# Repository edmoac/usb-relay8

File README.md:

# USB relay 8

KiCad project of USB relay board, using STM32 microcontroller.

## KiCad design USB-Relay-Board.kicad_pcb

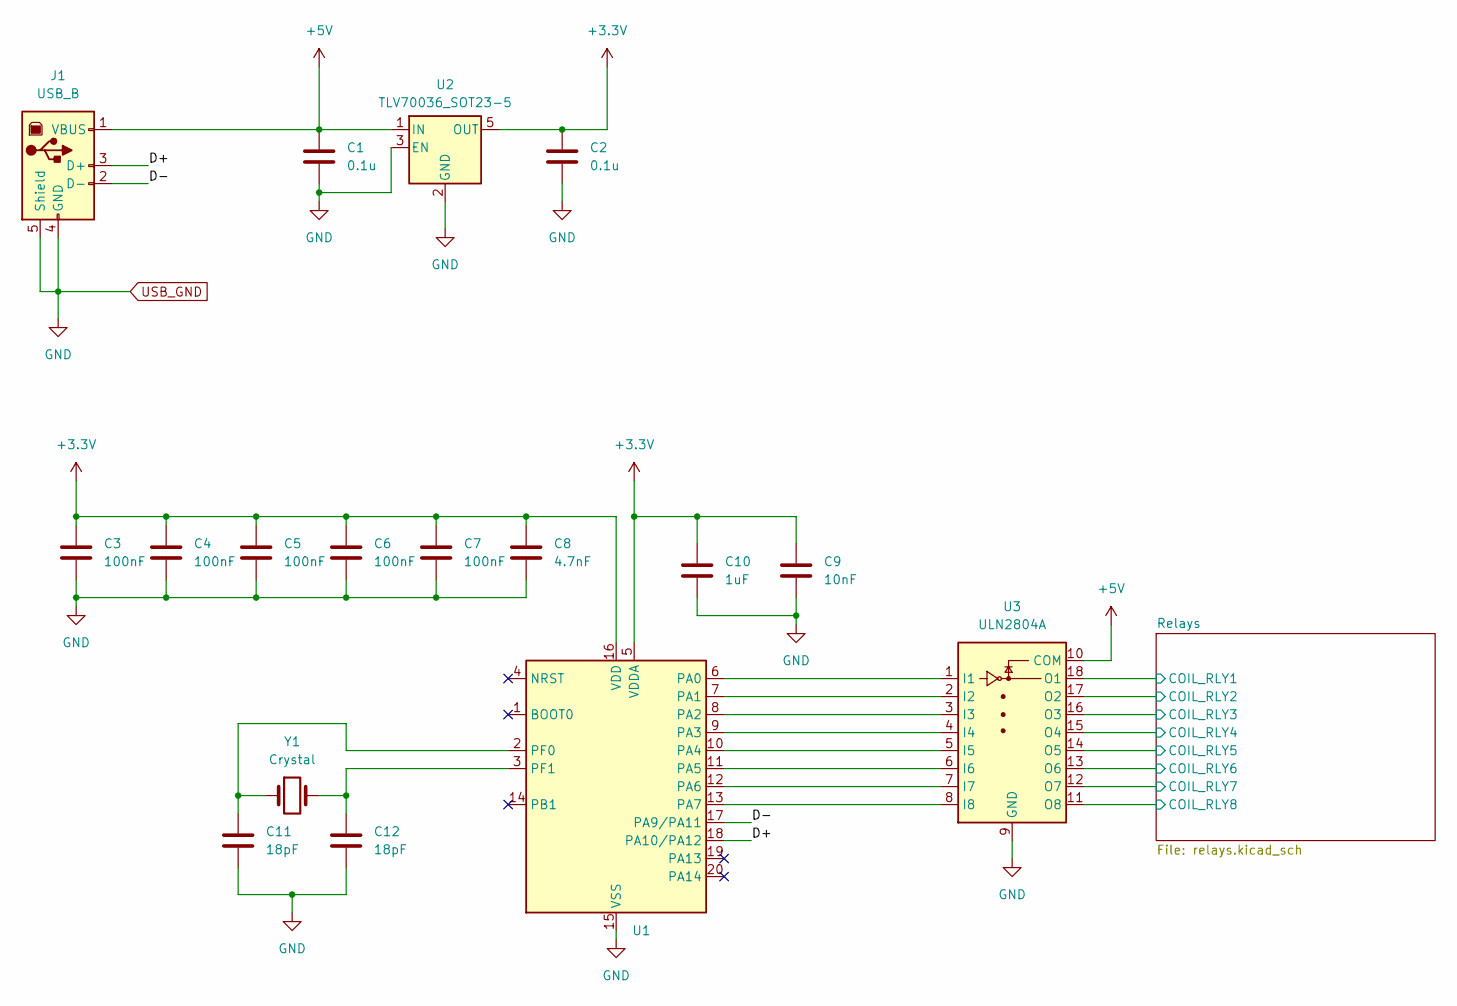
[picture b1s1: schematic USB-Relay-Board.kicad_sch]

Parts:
C1, C2: 0.1u; C_1206_3216Metric_Pad1.33x1.80mm_HandSolder
C3, C4, C5, C6, C7: 100nF; C_0805_2012Metric_Pad1.18x1.45mm_HandSolder
C8: 4.7nF; C_0805_2012Metric_Pad1.18x1.45mm_HandSolder
C9: 10nF; C_0805_2012Metric_Pad1.18x1.45mm_HandSolder
C10: 1uF; C_0805_2012Metric_Pad1.18x1.45mm_HandSolder
C11, C12: 18pF; C_0805_2012Metric_Pad1.18x1.45mm_HandSolder
J1: USB_B; USB_B_Lumberg_2411_02_Horizontal
U1: STM32F070F6Px; TSSOP-20_4.4x6.5mm_P0.65mm
U2: TLV70036_SOT23-5; SOT-23-5
U3: ULN2804A; DIP-18_W7.62mm_LongPads
Y1: Crystal; Crystal_HC18-U_Vertical

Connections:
+3.3V: C2.1, C3.1, C4.1, C5.1, C6.1, C7.1, C8.1, C9.1, C10.1, U1.5 (VDDA), U1.16 (VDD), U2.5 (OUT)
+5V: C1.1, J1.1 (VBUS), U2.1 (IN), U3.10 (COM)
/D+: J1.3 (D+), U1.18 (PA10/PA12)
/D-: J1.2 (D-), U1.17 (PA9/PA11)
/Relays/COIL_RLY1: U3.18 (O1); also elsewhere on the board
/Relays/COIL_RLY2: U3.17 (O2); also elsewhere on the board
/Relays/COIL_RLY3: U3.16 (O3); also elsewhere on the board
/Relays/COIL_RLY4: U3.15 (O4); also elsewhere on the board
/Relays/COIL_RLY5: U3.14 (O5); also elsewhere on the board
/Relays/COIL_RLY6: U3.13 (O6); also elsewhere on the board
/Relays/COIL_RLY7: U3.12 (O7); also elsewhere on the board
/Relays/COIL_RLY8: U3.11 (O8); also elsewhere on the board
unnamed: U1.6 (PA0), U3.1 (I1)
unnamed: U1.7 (PA1), U3.2 (I2)
unnamed: U1.8 (PA2), U3.3 (I3)
unnamed: U1.9 (PA3), U3.4 (I4)
unnamed: U1.10 (PA4), U3.5 (I5)
unnamed: U1.11 (PA5), U3.6 (I6)
unnamed: U1.12 (PA6), U3.7 (I7)
unnamed: U1.13 (PA7), U3.8 (I8)
unnamed: C11.1, U1.2 (PF0), Y1.1
unnamed: C12.1, U1.3 (PF1), Y1.2
USB_GND: C1.2, C2.2, C3.2, C4.2, C5.2, C6.2, C7.2, C8.2, C9.2, C10.2, C11.2, C12.2, J1.4 (GND), J1.5 (Shield), U1.15 (VSS), U2.2 (GND), U2.3 (EN), U3.9 (GND); also elsewhere on the board

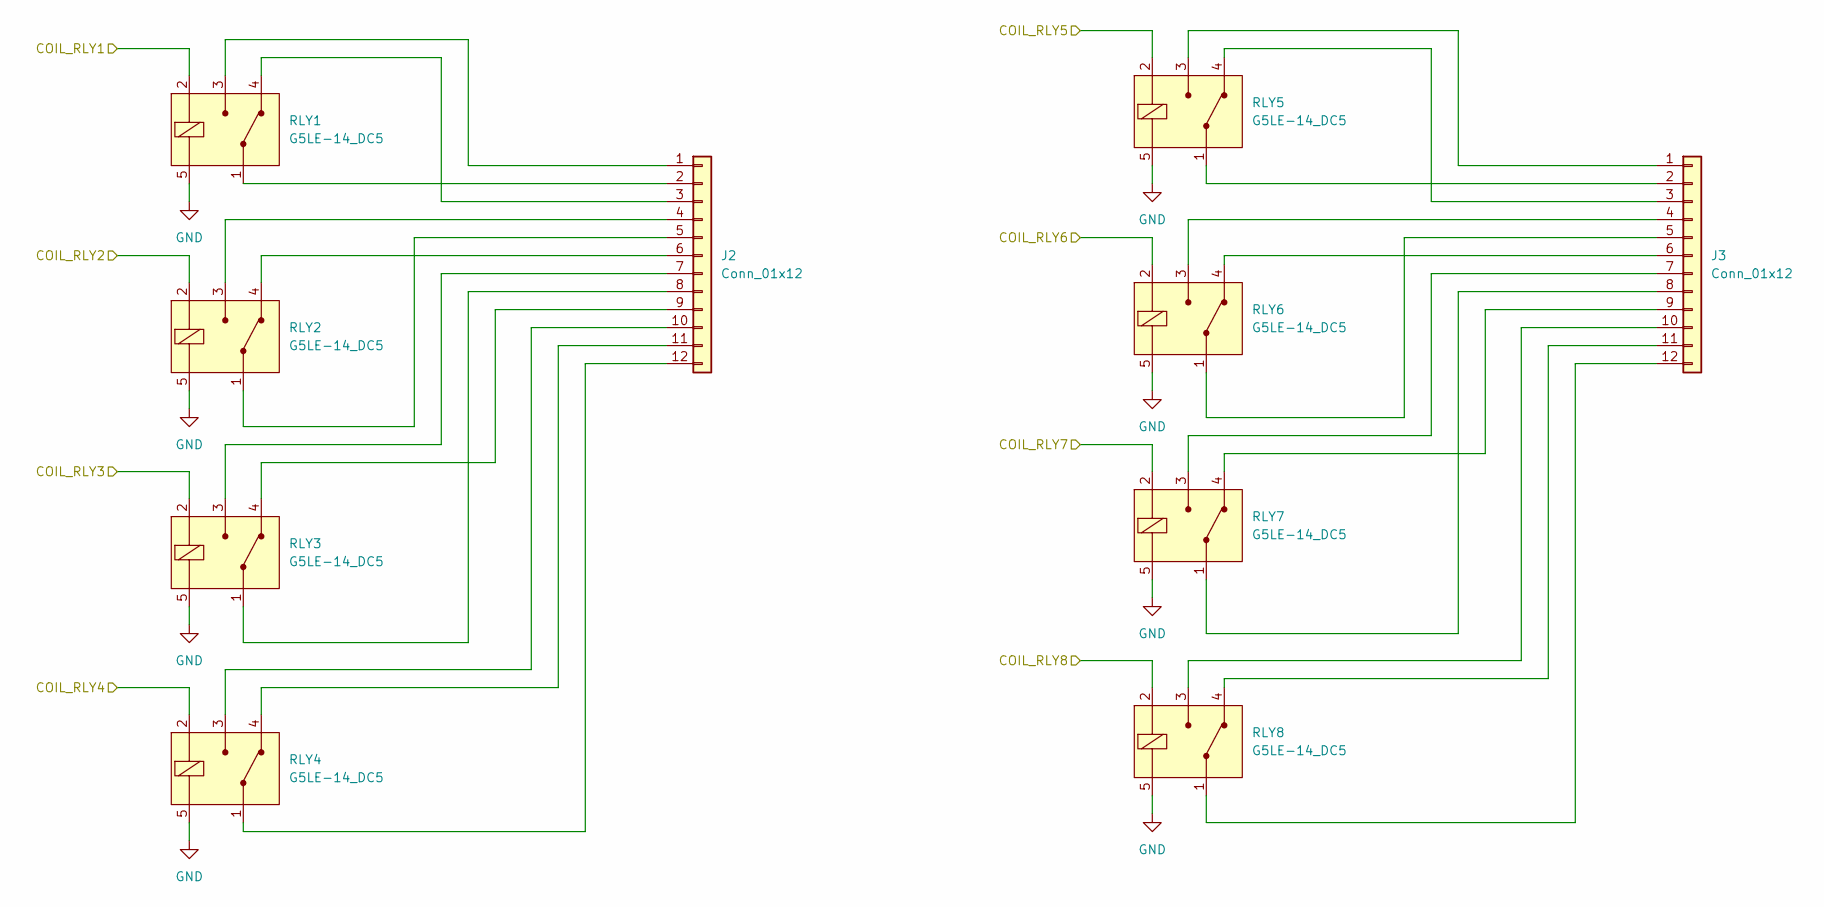
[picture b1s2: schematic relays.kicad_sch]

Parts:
J2, J3: Conn_01x12; PHOENIX_1935268
RLY1, RLY2, RLY3, RLY4, RLY5, RLY6, RLY7, RLY8: G5LE-14_DC5; Relay_THT_G5LE-14; MPN G5LE-14 DC5; Digi-Key_PN Z1011-ND

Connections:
/Relays/COIL_RLY1: RLY1.2 (COIL); also elsewhere on the board
/Relays/COIL_RLY2: RLY2.2 (COIL); also elsewhere on the board
/Relays/COIL_RLY3: RLY3.2 (COIL); also elsewhere on the board
/Relays/COIL_RLY4: RLY4.2 (COIL); also elsewhere on the board
/Relays/COIL_RLY5: RLY5.2 (COIL); also elsewhere on the board
/Relays/COIL_RLY6: RLY6.2 (COIL); also elsewhere on the board
/Relays/COIL_RLY7: RLY7.2 (COIL); also elsewhere on the board
/Relays/COIL_RLY8: RLY8.2 (COIL); also elsewhere on the board
unnamed: J2.1, RLY1.3 (NO)
unnamed: J2.2, RLY1.1 (COM)
unnamed: J2.3, RLY1.4 (NC)
unnamed: J2.4, RLY2.3 (NO)
unnamed: J2.5, RLY2.1 (COM)
unnamed: J2.6, RLY2.4 (NC)
unnamed: J2.7, RLY3.3 (NO)
unnamed: J2.8, RLY3.1 (COM)
unnamed: J2.9, RLY3.4 (NC)
unnamed: J2.10, RLY4.3 (NO)
unnamed: J2.11, RLY4.4 (NC)
unnamed: J2.12, RLY4.1 (COM)
unnamed: J3.1, RLY5.3 (NO)
unnamed: J3.2, RLY5.1 (COM)
unnamed: J3.3, RLY5.4 (NC)
unnamed: J3.4, RLY6.3 (NO)
unnamed: J3.5, RLY6.1 (COM)
unnamed: J3.6, RLY6.4 (NC)
unnamed: J3.7, RLY7.3 (NO)
unnamed: J3.8, RLY7.1 (COM)
unnamed: J3.9, RLY7.4 (NC)
unnamed: J3.10, RLY8.3 (NO)
unnamed: J3.11, RLY8.4 (NC)
unnamed: J3.12, RLY8.1 (COM)
USB_GND: RLY1.5 (COIL), RLY2.5 (COIL), RLY3.5 (COIL), RLY4.5 (COIL), RLY5.5 (COIL), RLY6.5 (COIL), RLY7.5 (COIL), RLY8.5 (COIL); also elsewhere on the board

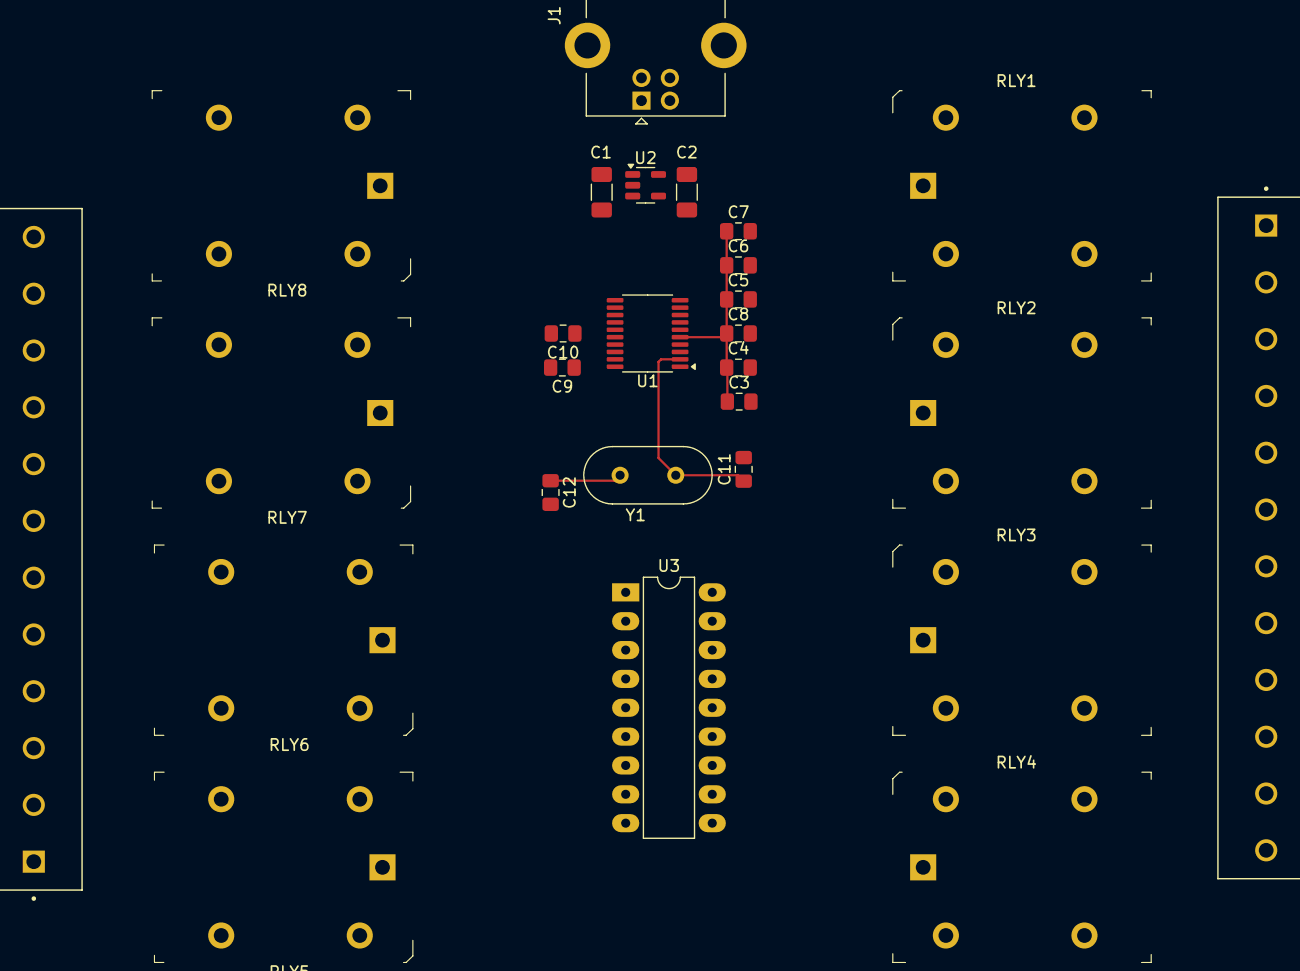
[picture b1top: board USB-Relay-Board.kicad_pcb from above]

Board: 2 copper layers, 27 parts (0 on the bottom side), 47 nets.

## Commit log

2024-10-23 Auto commit: Changes detected on 2024-10-22 20:06:29
2024-10-23 Auto commit: Changes detected on 2024-10-23 06:04:16
2024-10-23 Auto commit: Changes detected on 2024-10-23 06:16:01
2024-10-23 Auto commit: Changes detected on 2024-10-23 06:18:03
2024-11-20 adding pdf schematic
2024-11-20 19-nov
2024-11-20 Auto commit: Changes detected on 2024-11-19 20:08:07
2024-11-20 Auto commit: Changes detected on 2024-11-19 20:09:22
2024-11-20 Auto commit: Changes detected on 2024-11-19 20:10:01
